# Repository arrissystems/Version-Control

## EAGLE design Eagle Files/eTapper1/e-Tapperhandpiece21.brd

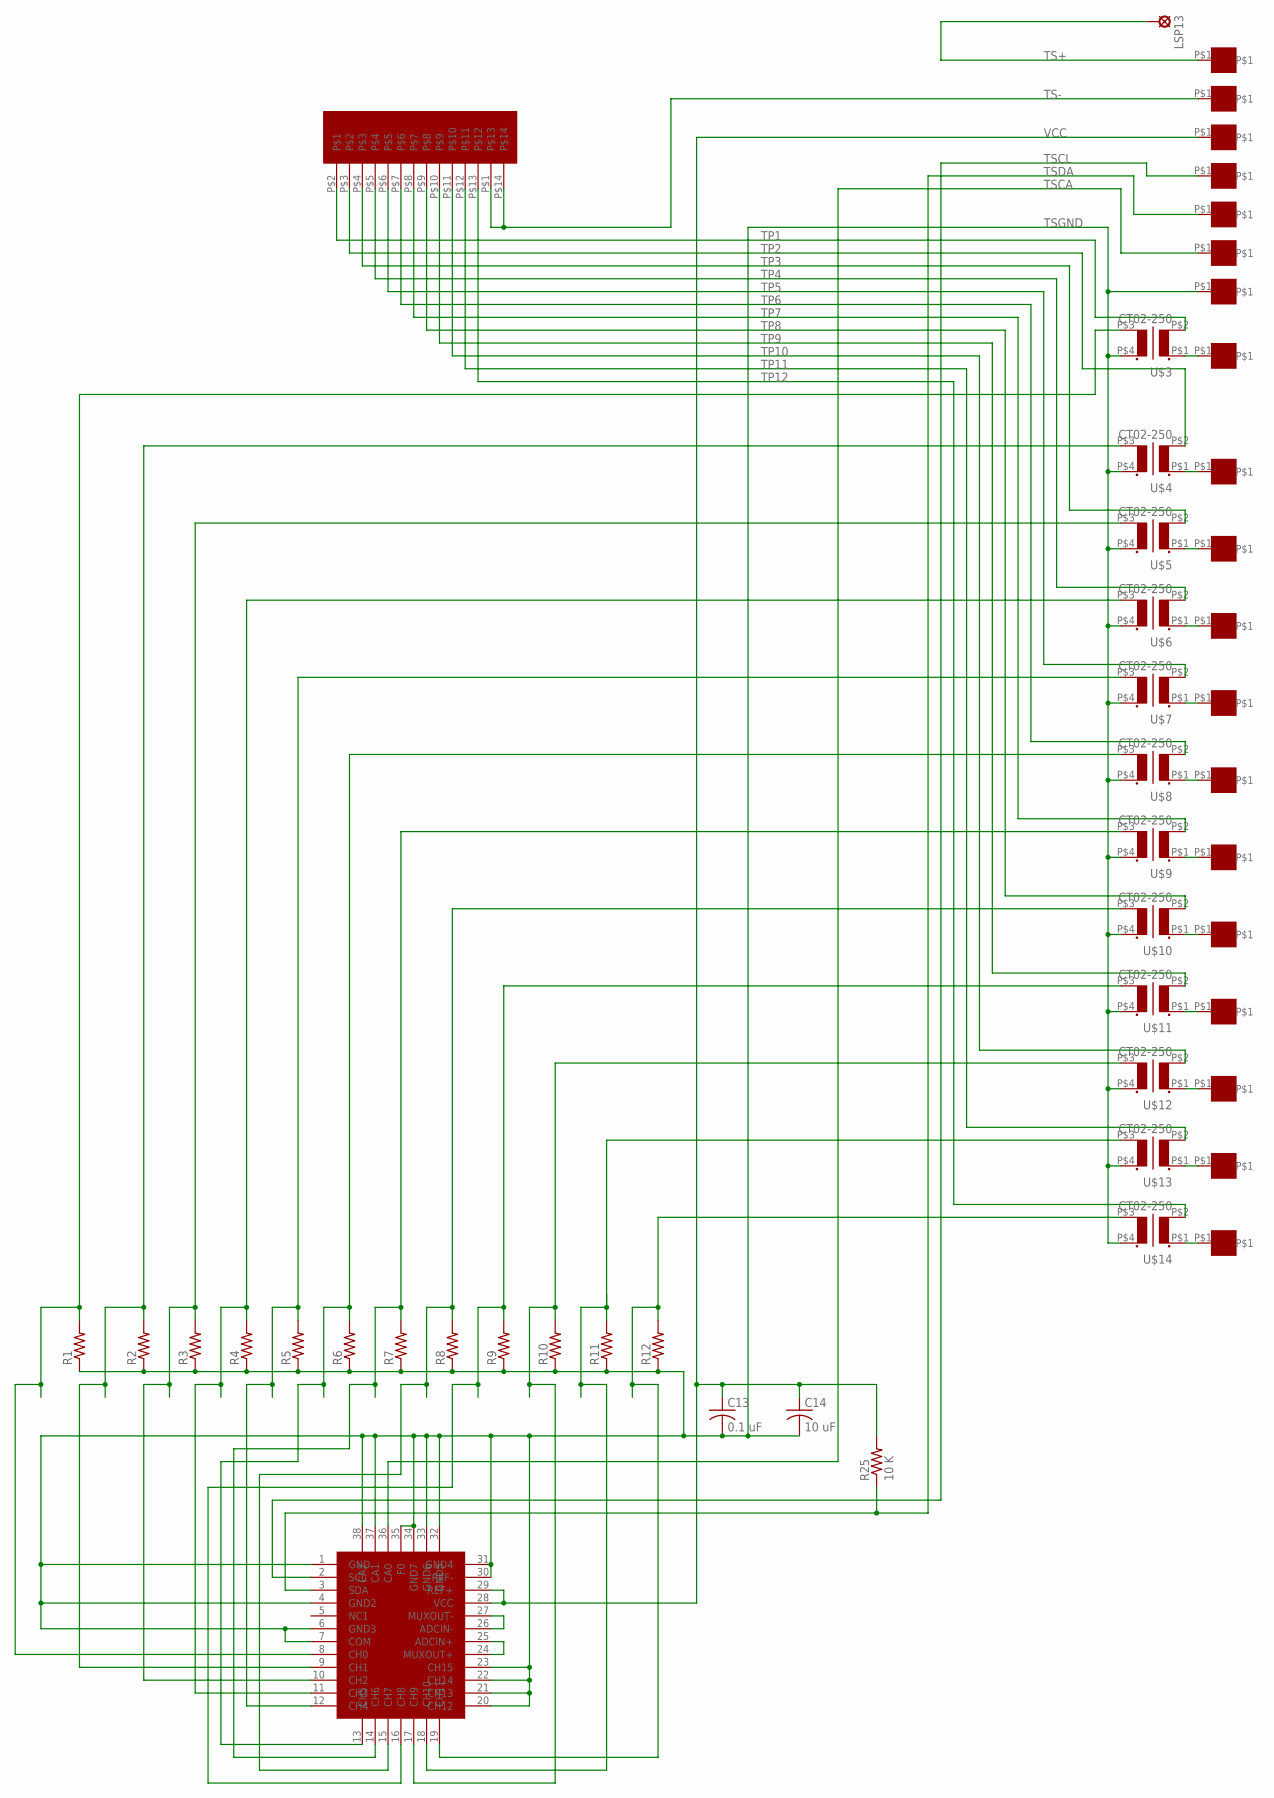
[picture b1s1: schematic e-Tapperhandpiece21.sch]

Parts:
C13: 0.1 uF; C0603
C14: 10 uF; C0805
LSP13: SE11
R1, R2, R3, R4, R5, R6, R7, R8, R9, R10, R11, R12: R-US_R0402; R0402
R25: 10 K; R0402
TSP1, TSP2, TSP3, TSP4, TSP5, TSP6, TSP7, TSP8, TSP9, TSP10, TSP11, TSP12, TSP13, TSP14, TSP15, TSP16, TSP17, TSP18, TSP19: ET1
U$1: LTC2497; QFN38-5X7
U$2: SS112D01
U$3, U$4, U$5, U$6, U$7, U$8, U$9, U$10, U$11, U$12, U$13, U$14: CT02-250

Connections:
unnamed: R9.2, U$1.16 (CH8), U$11.P$3 (S2)
unnamed: U$1.26 (ADCIN-), U$1.27 (MUXOUT-)
unnamed: U$1.24 (MUXOUT+), U$1.25 (ADCIN+)
unnamed: TSP1.P$1, U$3.P$1 (P1)
unnamed: R12.2, U$1.19 (CH11), U$14.P$3 (S2)
unnamed: TSP2.P$1, U$4.P$1 (P1)
unnamed: R4.2, U$1.11 (CH3), U$6.P$3 (S2)
unnamed: R10.2, U$1.17 (CH9), U$12.P$3 (S2)
unnamed: R8.2, U$1.15 (CH7), U$10.P$3 (S2)
unnamed: TSP3.P$1, U$5.P$1 (P1)
unnamed: TSP4.P$1, U$6.P$1 (P1)
unnamed: TSP5.P$1, U$7.P$1 (P1)
unnamed: TSP6.P$1, U$8.P$1 (P1)
unnamed: TSP7.P$1, U$9.P$1 (P1)
unnamed: TSP8.P$1, U$10.P$1 (P1)
unnamed: TSP9.P$1, U$11.P$1 (P1)
unnamed: TSP10.P$1, U$12.P$1 (P1)
unnamed: R5.2, U$1.12 (CH4), U$7.P$3 (S2)
unnamed: R6.2, U$1.13 (CH5), U$8.P$3 (S2)
unnamed: R7.2, U$1.14 (CH6), U$9.P$3 (S2)
unnamed: TSP11.P$1, U$13.P$1 (P1)
unnamed: R3.2, U$1.10 (CH2), U$5.P$3 (S2)
unnamed: R2.2, U$1.9 (CH1), U$4.P$3 (S2)
unnamed: R11.2, U$1.18 (CH10), U$13.P$3 (S2)
unnamed: R1.2, U$1.8 (CH0), U$3.P$3 (S2)
unnamed: TSP12.P$1, U$14.P$1 (P1)
TP1: U$2.P$2, U$3.P$2 (P2)
TP2: U$2.P$3, U$4.P$2 (P2)
TP3: U$2.P$4, U$5.P$2 (P2)
TP4: U$2.P$5, U$6.P$2 (P2)
TP5: U$2.P$6, U$7.P$2 (P2)
TP6: U$2.P$7, U$8.P$2 (P2)
TP7: U$2.P$8, U$9.P$2 (P2)
TP8: U$2.P$9, U$10.P$2 (P2)
TP9: U$2.P$10, U$11.P$2 (P2)
TP10: U$2.P$11, U$12.P$2 (P2)
TP11: U$2.P$12, U$13.P$2 (P2)
TP12: U$2.P$13, U$14.P$2 (P2)
TS+: LSP13.MP, TSP13.P$1
TS-: TSP14.P$1, U$2.P$1, U$2.P$14
TSCA: TSP18.P$1, U$1.36 (CA0)
TSCL: TSP16.P$1, U$1.2 (SCL)
TSDA: R25.1, TSP17.P$1, U$1.3 (SDA)
TSGND: C13.2, C14.2, R1.1, R2.1, R3.1, R4.1, R5.1, R6.1, R7.1, R8.1, R9.1, R10.1, R11.1, R12.1, TSP19.P$1, U$1.1 (GND), U$1.4 (GND2), U$1.6 (GND3), U$1.7 (COM), U$1.20 (CH12), U$1.21 (CH13), U$1.22 (CH14), U$1.23 (CH15), U$1.30 (REF-), U$1.31 (GND4), U$1.32 (GND5), U$1.33 (GND6), U$1.34 (GND7), U$1.35 (F0), U$1.37 (CA1), U$1.38 (CA2), U$3.P$4 (S1), U$4.P$4 (S1), U$5.P$4 (S1), U$6.P$4 (S1), U$7.P$4 (S1), U$8.P$4 (S1), U$9.P$4 (S1), U$10.P$4 (S1), U$11.P$4 (S1), U$12.P$4 (S1), U$13.P$4 (S1), U$14.P$4 (S1)
VCC: C13.1, C14.1, R25.2, TSP15.P$1, U$1.28 (VCC), U$1.29 (REF+)

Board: 2 copper layers, 49 parts (6 on the bottom side), 45 nets, no tracks yet.

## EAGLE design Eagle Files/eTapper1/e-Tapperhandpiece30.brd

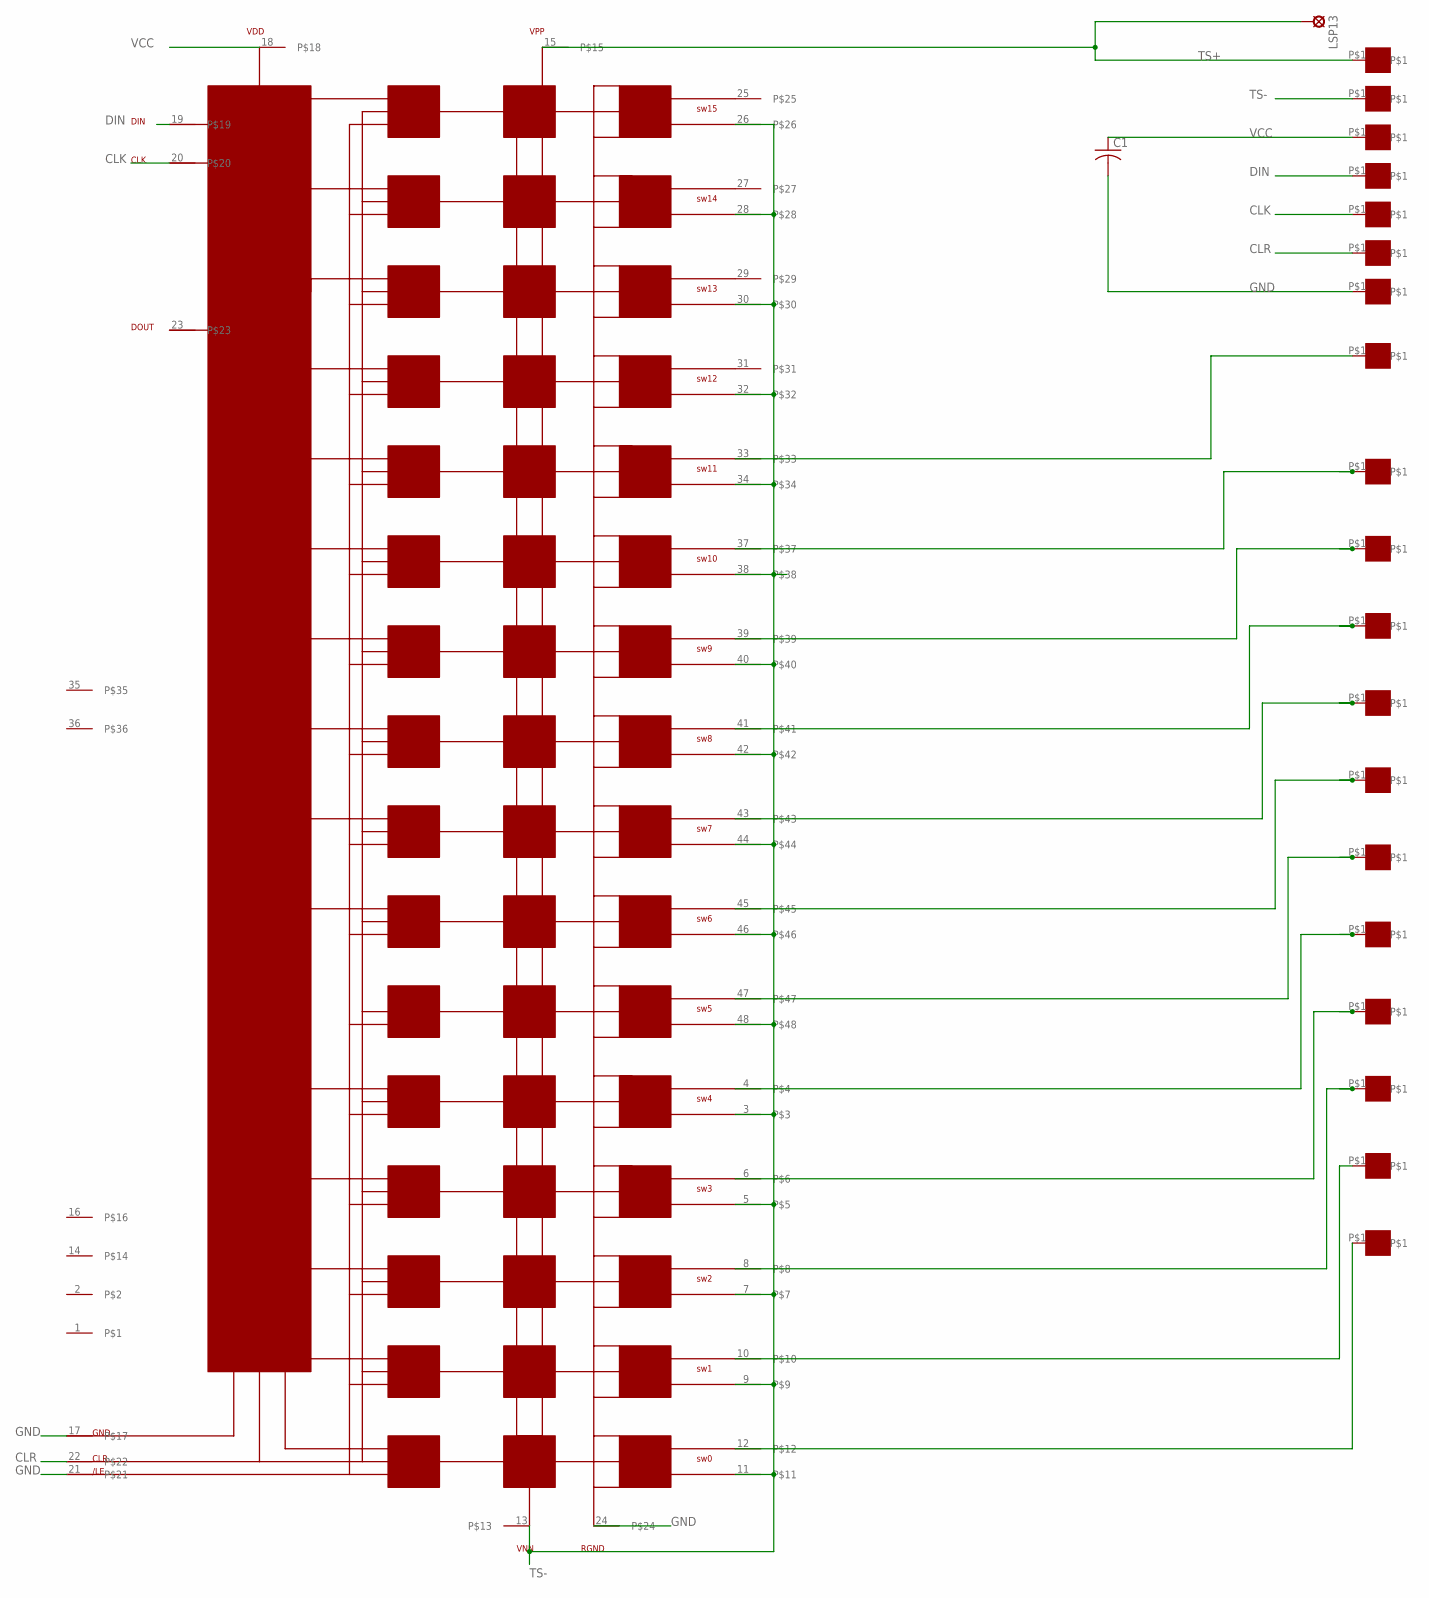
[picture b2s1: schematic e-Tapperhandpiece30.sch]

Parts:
C1: C-USC0805; C0805
LSP13: SE11
TSP1, TSP2, TSP3, TSP4, TSP5, TSP6, TSP7, TSP8, TSP9, TSP10, TSP11, TSP12, TSP13, TSP14, TSP15, TSP16, TSP17, TSP18, TSP19: ET1
U$1: CPC7701; LQFP48

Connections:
CLK: TSP17.P$1, U$1.20
CLR: TSP18.P$1, U$1.22
DIN: TSP16.P$1, U$1.19
GND: C1.2, TSP19.P$1, U$1.17, U$1.21, U$1.24
unnamed: TSP1.P$1, U$1.33
unnamed: TSP2.P$1, U$1.37
unnamed: TSP3.P$1, U$1.39
unnamed: TSP4.P$1, U$1.41
unnamed: TSP5.P$1, U$1.43
unnamed: TSP6.P$1, U$1.45
unnamed: TSP7.P$1, U$1.47
unnamed: TSP8.P$1, U$1.4
unnamed: TSP9.P$1, U$1.6
unnamed: TSP10.P$1, U$1.8
unnamed: TSP11.P$1, U$1.10
unnamed: TSP12.P$1, U$1.12
TS+: LSP13.MP, TSP13.P$1, U$1.15
TS-: TSP14.P$1, U$1.3, U$1.5, U$1.7, U$1.9, U$1.11, U$1.13, U$1.26, U$1.28, U$1.30, U$1.32, U$1.34, U$1.38, U$1.40, U$1.42, U$1.44, U$1.46, U$1.48
VCC: C1.1, TSP15.P$1, U$1.18

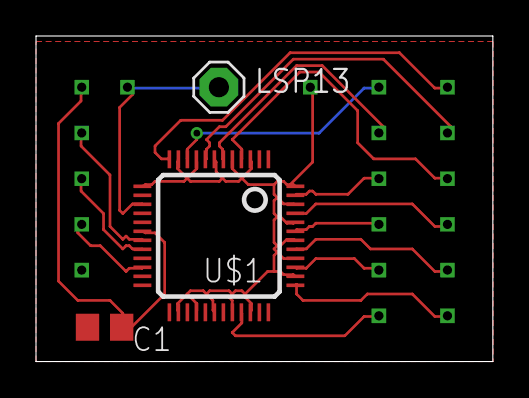
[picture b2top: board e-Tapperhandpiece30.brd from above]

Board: 2 copper layers, 25.4 x 18.1 mm, 22 parts (0 on the bottom side), 19 nets.

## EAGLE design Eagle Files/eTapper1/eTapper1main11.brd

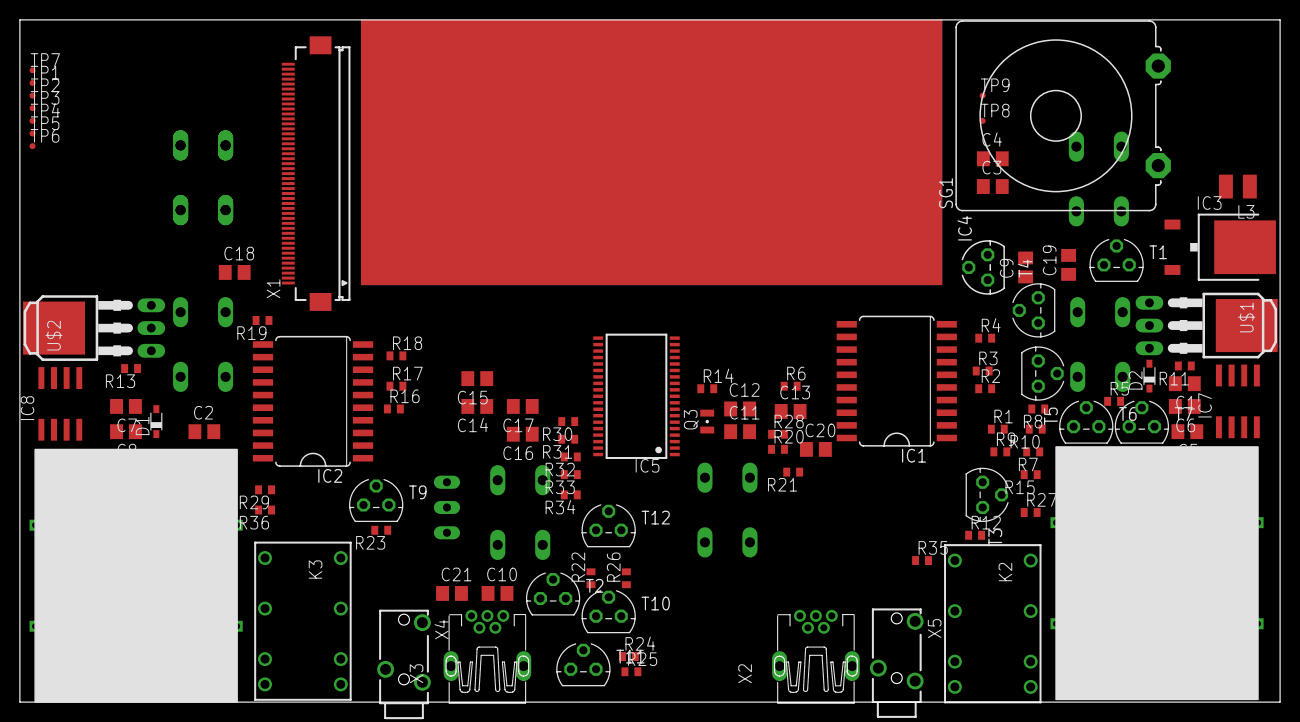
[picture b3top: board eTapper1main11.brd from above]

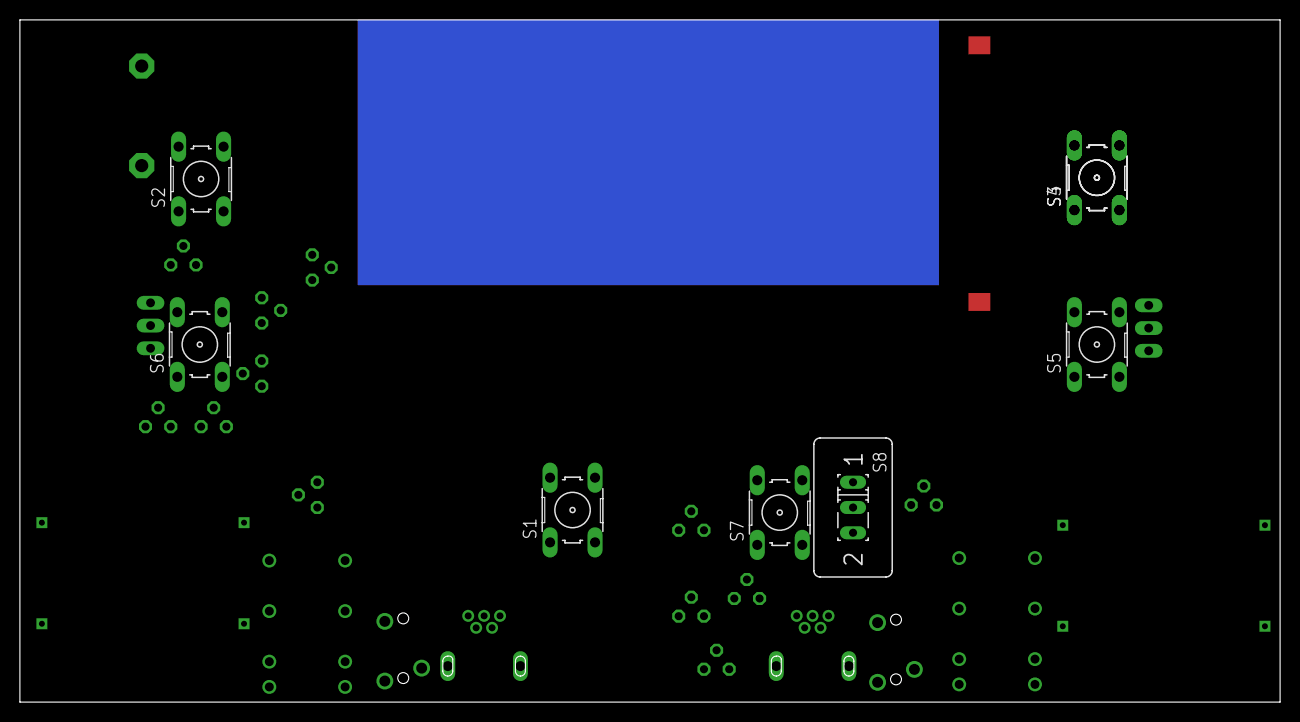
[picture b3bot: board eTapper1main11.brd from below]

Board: 2 copper layers, 126.7 x 68.6 mm, 108 parts (8 on the bottom side), 86 nets, no tracks yet.

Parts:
C1, C2, C3, C4, C5, C6, C7, C8, C9, C10, C11, C12, C13, C14, C15, C16, C17, C18, C19, C20, C21: C0805
D1, D2: BAT60J; SOD323_ST
IC1, IC2: 74AC373DW; SO20W
IC3: LM2936DT-5.0; TO252
IC4: LM2936Z-3.0; TO92
IC5: MSP430F2232IDA; TSSOP38_R-PDSO-G38-DA
IC7, IC8: LP2951M; SO08
K2, K3: DF2-DC3V; DF2
L3: L2825P
Q3: FC-12M
R1, R2, R3, R4, R5, R6, R7, R8, R9, R10, R11, R12, R13, R14, R15, R16, R17, R18, R19, R20, R21, R22, R23, R24, R25, R26, R27, R28, R29, R30, R31, R32, R33, R34, R35, R36: R0402
S1, S2, S3, S4, S5, S6, S7: B3F-10XX
S8: M251
SG1: B/C14L
T1, T2, T3, T4, T5, T6, T7, T9, T10, T11, T12: 2N3904; TO92
TP1, TP2, TP3, TP4, TP5, TP6, TP7, TP8, TP9: TPSTP06R; TP06R
U$1, U$2: IRLR024N; I-PAK_TO251AA
U$3, U$4: XFMR
X1: FH12-45S-0.5SH
X2, X3: MINI-USB_SHIELD5P2-32005-601; 32005-601
X4, X5: 1501_03

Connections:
+3V: C9.1, IC1.20, IC2.20, IC4.1, IC5.2, IC5.16, R20.2, R28.2, R29.2, R30.2, R31.2, R32.2, R33.2, R34.2, R36.2, TP5.TP, X1.2, X1.3, X3.4
+9V: C3.1, C4.1, IC3.1, IC4.3, IC5.28, IC7.8, IC8.8, TP8.TP
/LCS: IC5.8, X1.8
/RST: C13.1, IC5.7, R6.1
GND: C3.2, C4.2, C5.2, C6.2, C7.2, C8.2, C9.2, C10.2, C11.2, C12.2, C13.2, C14.2, C15.2, C16.2, C17.2, C18.2, C19.2, C20.2, C21.2, IC1.1, IC1.10, IC2.1, IC2.10, IC3.2, IC4.2, IC5.4, IC5.15, S1.4, S2.4, S3.4, S4.4, S5.4, S6.4, S7.4, S8.2, T1.3, T2.3, T3.3, T4.3, T5.3, T6.3, T7.3, T9.3, T10.3, T11.3, T12.3, TP7.TP, TP9.TP, U$1.3, U$2.3, X1.1, X1.4, X1.5, X1.6, X1.12, X1.13, X1.14, X1.15, X1.16, X1.25, X1.26, X1.27, X1.28, X1.29, X1.30, X1.31, X1.32, X1.33, X1.34, X1.45, X2.4, X2.5, X3.5
IO1_0: C14.1, IC5.31, R28.1, S1.2
IO1_1: C15.1, IC5.32, R29.1, S2.2
IO1_2: C16.1, IC5.33, R30.1, S3.2
IO1_3: C17.1, IC5.34, R31.1, S4.2
IO4_0: IC1.3, IC2.3, IC5.17, X1.17
IO4_1: IC1.4, IC2.4, IC5.18, X1.18
IO4_2: IC1.7, IC2.7, IC5.19, X1.19
IO4_3: IC1.8, IC2.8, IC5.20, X1.20
IO4_4: IC1.13, IC2.13, IC5.21, X1.21
IO4_5: IC5.22, X1.22
IO4_6: IC5.23, X1.23
IO4_7: IC5.24, X1.24
J2_1: K2.3, R12.1, U$3.P$3
J2_3: K2.10, R12.2, U$3.P$4
J3_1: K3.3, R27.1, U$4.P$3
J3_3: K3.10, R27.2, U$4.P$4
LD_/C: IC5.29, X1.9
LHVTRIG: IC5.30, R13.1
LRD: IC5.10, X1.11
LRESET: IC5.26, X1.7
LTS+: K2.8, X4.1
LTS-: K2.5, X4.3
LVSEL: IC1.11, IC5.14
LWR: IC5.9, X1.10
unnamed: IC1.2, R1.1
unnamed: IC1.5, R2.1
unnamed: IC1.6, R3.1
unnamed: IC1.9, R4.1
unnamed: IC1.12, R5.1
unnamed: L3.2, SG1.1, T1.1
unnamed: R4.2, T6.2
unnamed: R5.2, T7.2
unnamed: D2.A, U$1.2, U$1.4, U$3.P$1
unnamed: R7.1, T3.1
unnamed: R8.1, T4.1
unnamed: R9.1, T5.1
unnamed: R1.2, T3.2
unnamed: R2.2, T4.2
unnamed: R3.2, T5.2
unnamed: R10.1, T6.1
unnamed: C1.2, IC7.7, R7.2, R8.2, R9.2, R10.2, R11.2
unnamed: C1.1, C5.1, C6.1, D2.C, IC7.1, R11.1, U$3.P$2
unnamed: D1.A, U$2.2, U$2.4, U$4.P$1
unnamed: IC2.2, R15.1
unnamed: R13.2, U$1.1
unnamed: R14.2, T1.2
unnamed: R35.1, S8.1
unnamed: IC2.5, R16.1
unnamed: IC2.6, R17.1
unnamed: IC2.9, R18.1
unnamed: IC2.12, R19.1
unnamed: R15.2, T2.2
unnamed: R16.2, T9.2
unnamed: R17.2, T10.2
unnamed: R18.2, T11.2
unnamed: R19.2, T12.2
unnamed: K2.1, K3.1, R35.2
unnamed: R22.1, T2.1
unnamed: R23.1, T9.1
unnamed: R24.1, T10.1
unnamed: R25.1, T11.1
unnamed: C2.2, IC8.7, R22.2, R23.2, R24.2, R25.2, R26.2
unnamed: C2.1, C7.1, C8.1, D1.C, IC8.1, R26.1, U$4.P$2
unnamed: R21.2, U$2.1
unnamed: IC7.4, T7.1
unnamed: IC8.4, T12.1
RHVTRIG: IC5.3, R21.1
RTS+: K3.8, X5.1
RTS-: K3.5, X5.3
RVSEL: IC2.11, IC5.25
SCL: IC5.13, X2.2, X3.2
SDA: IC5.12, X2.3, X3.3
SPKR: IC5.11, R14.1
TCK: C18.1, IC5.35, R32.1, S5.2, TP4.TP
TDI: C20.1, IC5.37, R34.1, S7.2, TP2.TP
TDO: C21.1, IC5.38, R36.1, S8.3, TP1.TP
TEST: IC5.1, R20.1, TP6.TP
TMS: C19.1, IC5.36, R33.1, S6.2, TP3.TP
VCC: C10.1, IC3.3, K2.7, K2.12, K3.7, K3.12, L3.1, R6.2, SG1.2, X2.1, X3.1
XIN: C12.1, IC5.6, Q3.2
XOUT: C11.1, IC5.5, Q3.1
